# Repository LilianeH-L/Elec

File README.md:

# Metis-Elec

Repositories pour de le code de l'équipe électrique les trois équipes sont : 

- Acquisiton 
    - Capter les signaux EMG du patient pour le transmettre au Jetson

- Moor_Control
    - Contrôle de la position de tous les moteurs pour ateindre la position désiré

- BLDC_Driver
    - Contrôle individuelle de chaque moteur BLDC pour qu'il soit à la position recquise.

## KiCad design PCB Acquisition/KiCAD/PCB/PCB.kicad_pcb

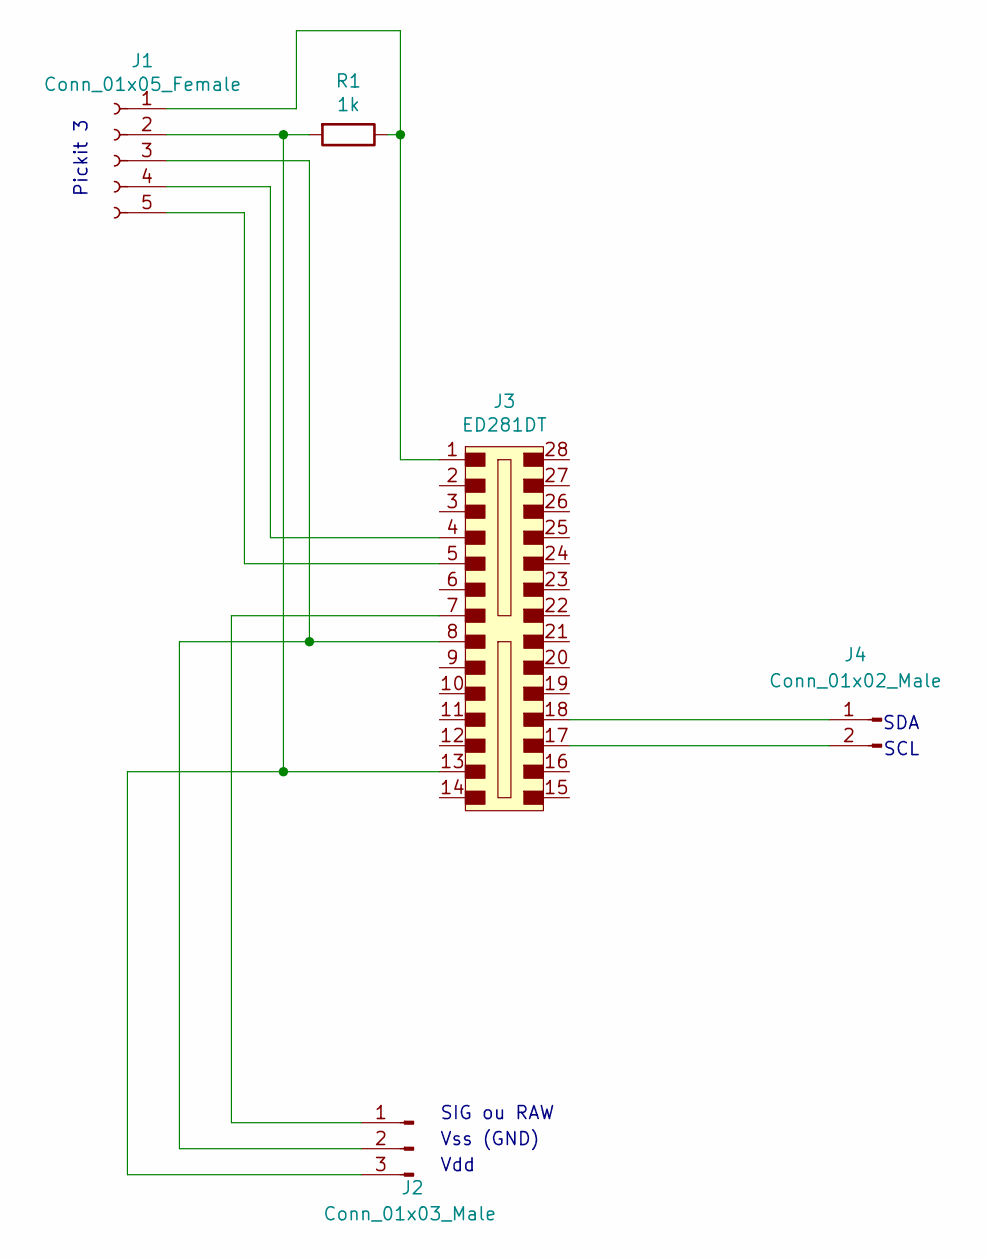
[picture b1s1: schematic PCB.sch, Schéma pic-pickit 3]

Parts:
J1: Conn_01x05_Female; PinSocket_1x06_P2.54mm_Vertical
J2: Conn_01x03_Male; PinHeader_1x03_P2.54mm_Vertical
J3: ED281DT; Socket_DIP-28_7.62mm_Conn; MPN ED281DT; Digi-Key_PN ED3050-5-ND
J4: Conn_01x02_Male; Molex_KK-396_A-41791-0002_1x02_P3.96mm_Vertical
R1: 1k; R_Axial_DIN0207_L6.3mm_D2.5mm_P7.62mm_Horizontal

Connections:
unnamed: J1.1, J3.1, R1.1
unnamed: J1.2, J2.3, J3.13, R1.2
unnamed: J1.3, J2.2, J3.8
unnamed: J1.4, J3.4
unnamed: J1.5, J3.5
unnamed: J2.1, J3.7
unnamed: J3.17, J4.2
unnamed: J3.18, J4.1

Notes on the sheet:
SIG ou RAW
Vss (GND)
Vdd
Pickit 3
SDA
SCL

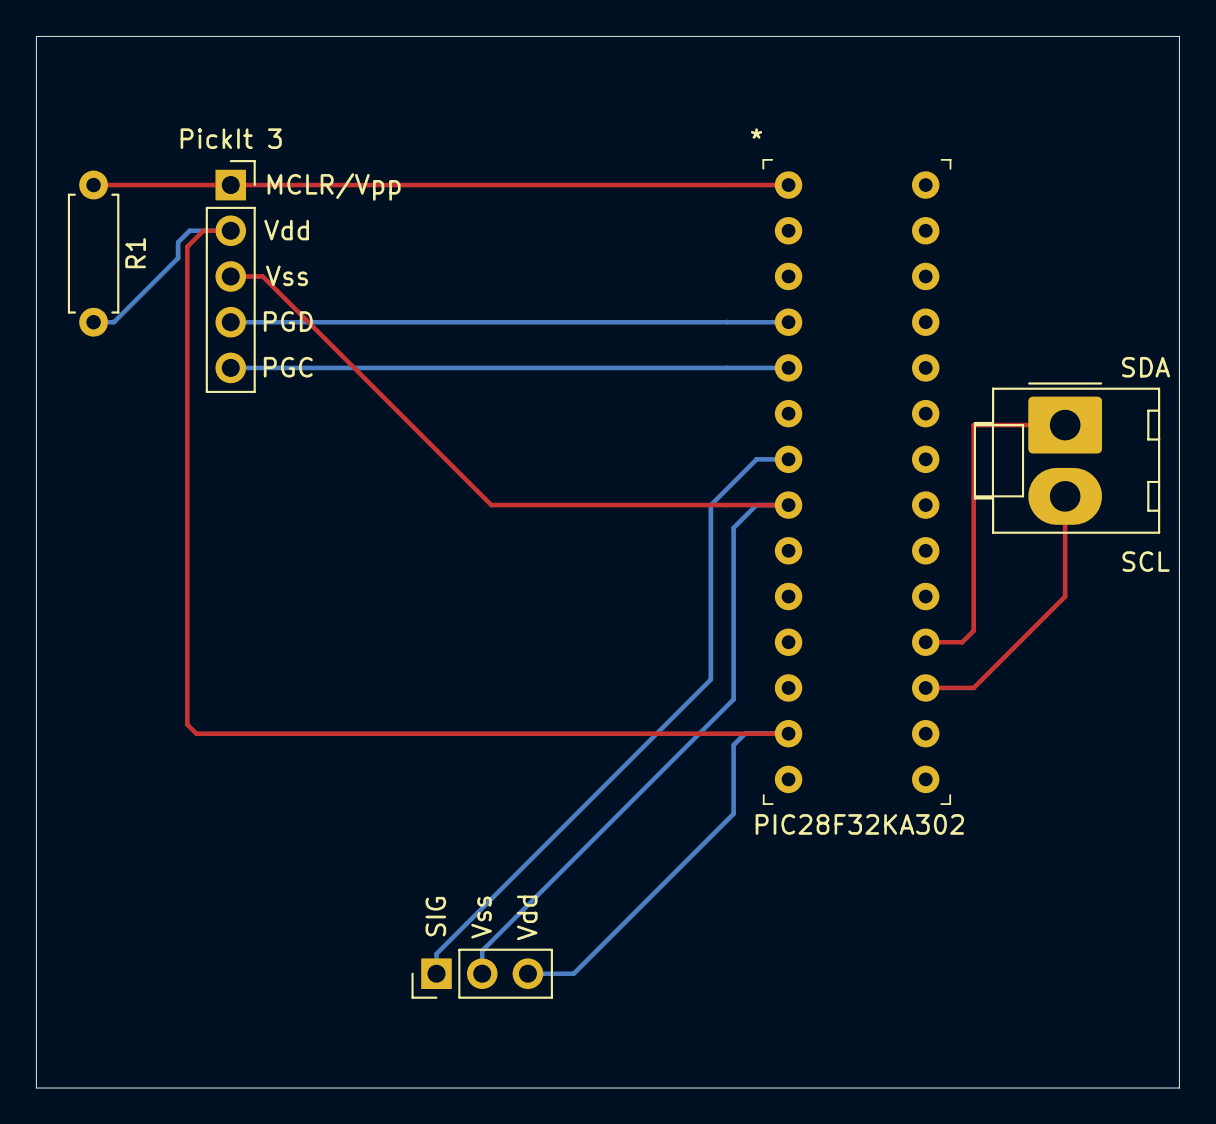
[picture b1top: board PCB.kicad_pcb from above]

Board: 2 copper layers, 63.5 x 58.4 mm, 5 parts (0 on the bottom side), 8 nets.

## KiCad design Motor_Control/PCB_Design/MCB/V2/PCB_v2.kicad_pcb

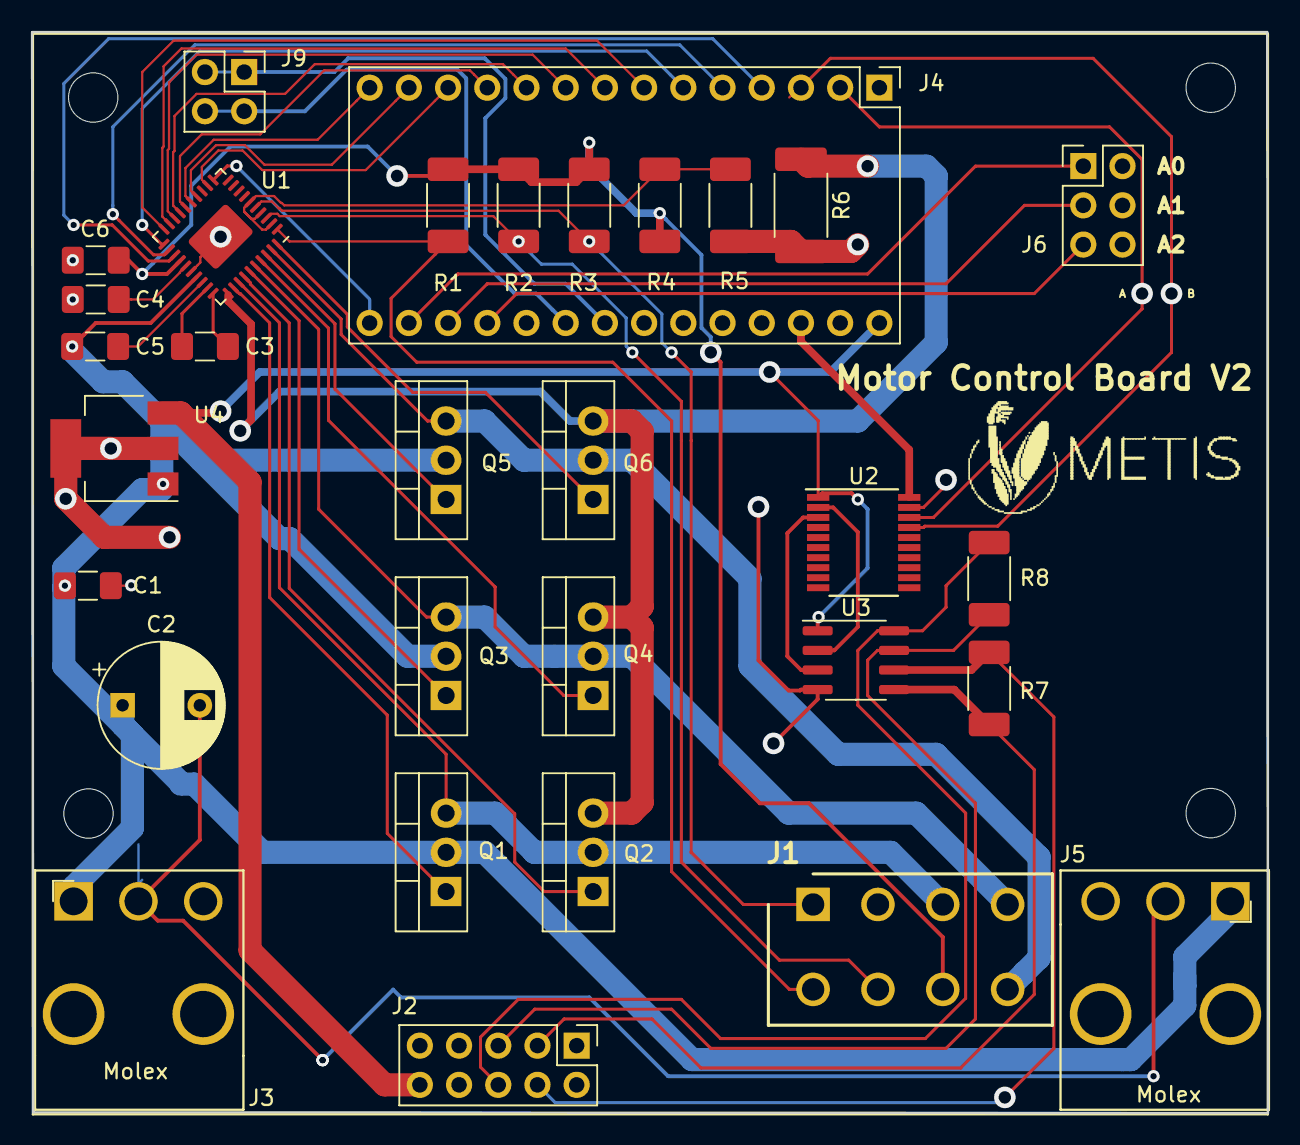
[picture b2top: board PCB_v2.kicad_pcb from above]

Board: 2 copper layers, 80.1 x 70.0 mm, 32 parts (0 on the bottom side), 48 nets.

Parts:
C1, C3, C6: 0.1uF; C_1206_3216Metric_Pad1.42x1.75mm_HandSolder
C2: 470uF; CP_Radial_D8.0mm_P5.00mm
C4, C5: 1uF; C_1206_3216Metric_Pad1.42x1.75mm_HandSolder
J1: Molex_Motor; SHDR8W125P550X420_2X4_1800X960X1310P
J2: Conn_Encoder; PinHeader_2x05_P2.54mm_Vertical
J3: Molex_Pwr_In; Molex,1x3
J4: Teensy; TeensyLC
J5: Molex_Pwr_Out; Molex,1x3,Right
J6: Adress_Pins; PinHeader_2x03_P2.54mm_Vertical
J9: Conn_I2C; PinSocket_2x02_P2.54mm_Vertical
LOGO: logo_metis
Q1, Q2, Q3, Q4, Q5, Q6: Q_NMOS_IRLB8743; TO-220-3_Vertical
R1, R2, R3, R4, R5: 1K; R_2010_5025Metric_Pad1.52x2.65mm_HandSolder
R6: 0.025; R_2512_6332Metric_Pad1.52x3.35mm_HandSolder
R7, R8: 120; R_2010_5025Metric_Pad1.52x2.65mm_HandSolder
U1: DRV8308; Texas_S-PVQFN-N40_EP3.52x2.62mm
U2: SN74LVC245APWE4; TSSOP-20_4.4x6.5mm_P0.65mm
U3: SN65LVDT34D-MyLibrary; SOIC-8_3.9x4.9mm_P1.27mm
U4: LM2931; SOT-223-3_TabPin2

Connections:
/3.3V: J4.26, U2.20
/A: J4.2, U2.18
/B: J4.3, U2.17
/BRAKE: J4.7, U1.20
/CLKIN: J4.8, U1.19
/DATAI: J4.13, U1.14
/DATAO: J4.14, U1.15
/DIR: J4.6, U1.21
/ENABLE: J4.5, U1.22
/ENC_!A: J2.5, R8.2, U3.7
/ENC_!B: J2.3, R7.1, U3.5
/ENC_A: J2.6, R8.1, U3.8
/ENC_B: J2.4, R7.2, U3.6
/FAULTn: J4.10, U1.17
/FGOUT: J4.11, U1.16
/Hall_1: J1.5, R1.2, U1.1
/Hall_2: J1.6, R2.2, U1.3
/Hall_3: J1.1, R3.2, U1.5
/LOCKn: J4.9, U1.18
/MCU/A0: J4.16, J6.1
/MCU/A1: J4.17, J6.3
/MCU/A2: J4.18, J6.5
/Power/ISEN: Q2.3, Q4.3, Q6.3, R6.1, U1.31
/Power/UHSG: Q1.1, U1.32
/Power/ULSG: Q2.1, U1.34
/Power/VHSG: Q3.1, U1.35
/Power/VLSG: Q4.1, U1.37
/Power/WHSG: Q5.1, U1.38
/Power/WLSG: Q6.1, U1.40
/RESET: J4.4, U1.23
/SCL: J4.21, J9.1, J9.2
/SCLK: J4.15, U1.11
/SCS: J4.12, U1.12
/SDA: J4.20, J9.3, J9.4
/UHN: R4.2, R5.1, U1.2, U1.4, U1.6
/Vin: J2.10, J4.28, U2.1, U3.1, U4.3
/Vm: C1.1, C2.1, C5.1, J3.1, J5.1, Q1.2, Q3.2, Q5.2, U1.27, U4.1
/Vreg: C6.2, J1.7, R1.1, R2.1, R3.1, R4.1, U1.24
GNDREF: C1.2, C2.2, C4.1, C6.1, J1.2, J2.7, J3.2, J4.1, J4.27, J5.2, J6.2, J6.4, J6.6, R5.2, R6.2, U1.26, U1.41, U2.19, U3.4, U4.2
Motor_1: J1.3, Q1.3, Q2.2, U1.33
Motor_2: J1.4, Q3.3, Q4.2, U1.36
Motor_3: J1.8, Q5.3, Q6.2, U1.39
unnamed: C3.1, U1.30
unnamed: C3.2, U1.29
unnamed: C4.2, U1.25
unnamed: C5.2, U1.28
unnamed: U2.2, U3.2
unnamed: U2.3, U3.3

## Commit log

2019-09-03 Files setup
2019-10-03 Rename folder
2019-10-03 Folder management
2019-10-24 test
2019-10-24 supprimer le test
2019-10-27 Tentative de mettre les codes
2019-10-30 New project setup
2019-10-30 Début du nouveau code
2019-10-31 Test sur code
2019-10-31 test d'un txt
2019-10-31 Add folder
2019-10-31 modification 1
2019-10-31 Auto stash before merge of "develop-biomeca" and "origin/develop-biomeca"
2019-10-31 typo
2019-10-31 Add files via upload
    Code de lecture d'un encodeur
2019-10-31 changement dans ma branche
2019-10-31 Add serialCom file
2019-10-31 Revert "Develop biomeca"
2019-10-31 Travail sur le code
2019-11-01 New Motor Datasheet
2019-11-01 Header files creation
2019-11-07 Schema 2 Sophie ajout rég tension (pas bonnes pins)
2019-11-07 Prog de sauvegarde des données (pour l'instant juste le chargement de données depuis un csv + organisation)
2019-11-08 Schema 2 Manu ajout LED
2019-11-08 Schéma 2, modification de U2 et U3 pour les nouveaux models + ajustement de l'orientation des connecteurs molex
2019-11-08 Footprint 2, tous ajoutés sauf les LED + Swtich
2019-11-10 Code python 2 articulation
    Les angles ne sont pas bon mais je ne sais pas pourquoi
2019-11-11 Code
2019-11-13 Footprint des résistances pour les LEDS
    Voir pour la PCB 1.5, car je crois que tout est prêt
2019-11-14 Changement des fichiers liveplot_joint, plus beau, prompt
2019-11-14 Nouveau design de la board
    **Pas trouvé de façon de générer une nouvelle board encore, donc repositionnement fait mais il faut arranger les tracks et tout le reste
2019-11-14 Début de la nouvelle board
    Les molex, teensy et autres ne loadent pas sur mon ordi
2019-11-14 RIP LEDS
2019-11-14 PCB à jour, track manquante
2019-11-14 PBC avec groundplane et labels placés, tracks manquantes
2019-11-14 Début tracks
2019-11-15 All routs
2019-11-15 Debut code I2C
2019-11-15 Board finit!
2019-11-16 Rename Sauvegarde.py to Lecture_donnees.py
2019-11-16 Ajout du time stamp
2019-11-16 Petite correction
2019-11-17 Correction encore
2019-11-17 Create Lecture_form_npy and comment SerialCom (juste un peu)
2019-11-18 Commentaires serialCom
2019-11-21 Modifications serial com et lecture encodeurs
    correction de valeurs dans lecture teensy et serial com
2019-11-21 Notre SerialCom
2019-11-24 Ecriture et lecture des donnees (Teensy et SerialCom) - manque juste le temps à ajouter dans SerialCom
2019-11-24 Corrections et ajout du temps
2019-11-25 Corrections de SerialCom2 et code de lecture des données depuis .npy
2019-11-25 Rencontre 25 novembre
    Test de serialCom2.py et lecture npy, problèmes relevés
2019-11-25 Juste changé jusqu'où on parcourt 'position'
2019-11-28 codes i2c
    ajout du code master writer, master reader et slave
2019-11-28 Debug SerialCom2 et Lecture_from_npy
2019-12-02 Code fonctionnel : Démo
2019-12-02 Demo 2
2019-12-09 Genial demo2
2020-01-29 Fix du prob de ground
2020-01-29 Plus de code
2020-01-30 Platform version specify
2020-02-05 Code de test basic
2020-02-13 added motor angle test
2020-02-14 Code clean up
    Don't know what the methods in the controller section are for
2020-02-20 added test functions
2020-02-20 Ajout du Readme
2020-02-20 Tasks update
2020-02-20 incrementation vitesse
2020-02-20 Added goToAngle with more parameters
2020-02-29 Fonction vitesse
    fonction qui output la vitesse en angle/ms
2020-03-05 Added PID for the angle
    Still need to find the right tuning parameters
2020-03-12 update gitignore
2020-03-12 gitignore 2
2020-03-12 working on general test
2020-03-12 fonctions de test
2020-03-13 Tuning parameters determined
    changed input value to angle instead of error
2020-04-10 Début du PCB
2020-04-10 [Acquisition] Upload des fichiers KiCad de la chip du microcontrôleur
2020-04-10 Début du PCB avec les fichiers téléchargés d'internet
2020-05-06 [Acquisition] Ajout des fichiers MPLab pour programmer le PIC
2020-09-24 Développement du PCB
    Ajout du pickit au schéma et début du circuit
2020-10-07 Ajout fichiers structure
2020-10-22 Ajout des connections pour I2C sur le schéma
    Ajout des connections pour I2C SCL et SDA sur le schéma
2020-11-04 update tests
2020-11-04 update tests
    ajustement accélération et décélération
2020-11-05 Ajout de l'électrode au schéma
    Les connexions nécessaires pour lier le PIC et l'électrode ont été ajoutées au schéma
2020-11-12 update main
2020-11-18 Update Delta angle
    Correction mineure
2020-11-19 compilation ok
2020-11-25 début pid.cpp
2021-01-21 Début du layout
    Les pièces ont été choisies pour le PCB et le layout du PCB avec celles-ci est commencé. Il reste à finaliser le layout.
2021-01-28 PCB Layout
    Layout du PCB
2021-02-03 Poursuite du layout (tracks)
    Les tracks sont finies.
2021-02-10 PCB fini
2021-03-17 pid upgrade
2021-04-01 pid fonctionnel
2021-04-17 pid avec variable globale
2021-04-17 Ajout de commentaires (TODO)
